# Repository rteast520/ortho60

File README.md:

This is a pcb design and eventual firmware for an ortholinear 60% hall effect keyboard. To my knowledge there currently are no hall effect ortholinear keyboards for purchase so feel free to take this and run with it.

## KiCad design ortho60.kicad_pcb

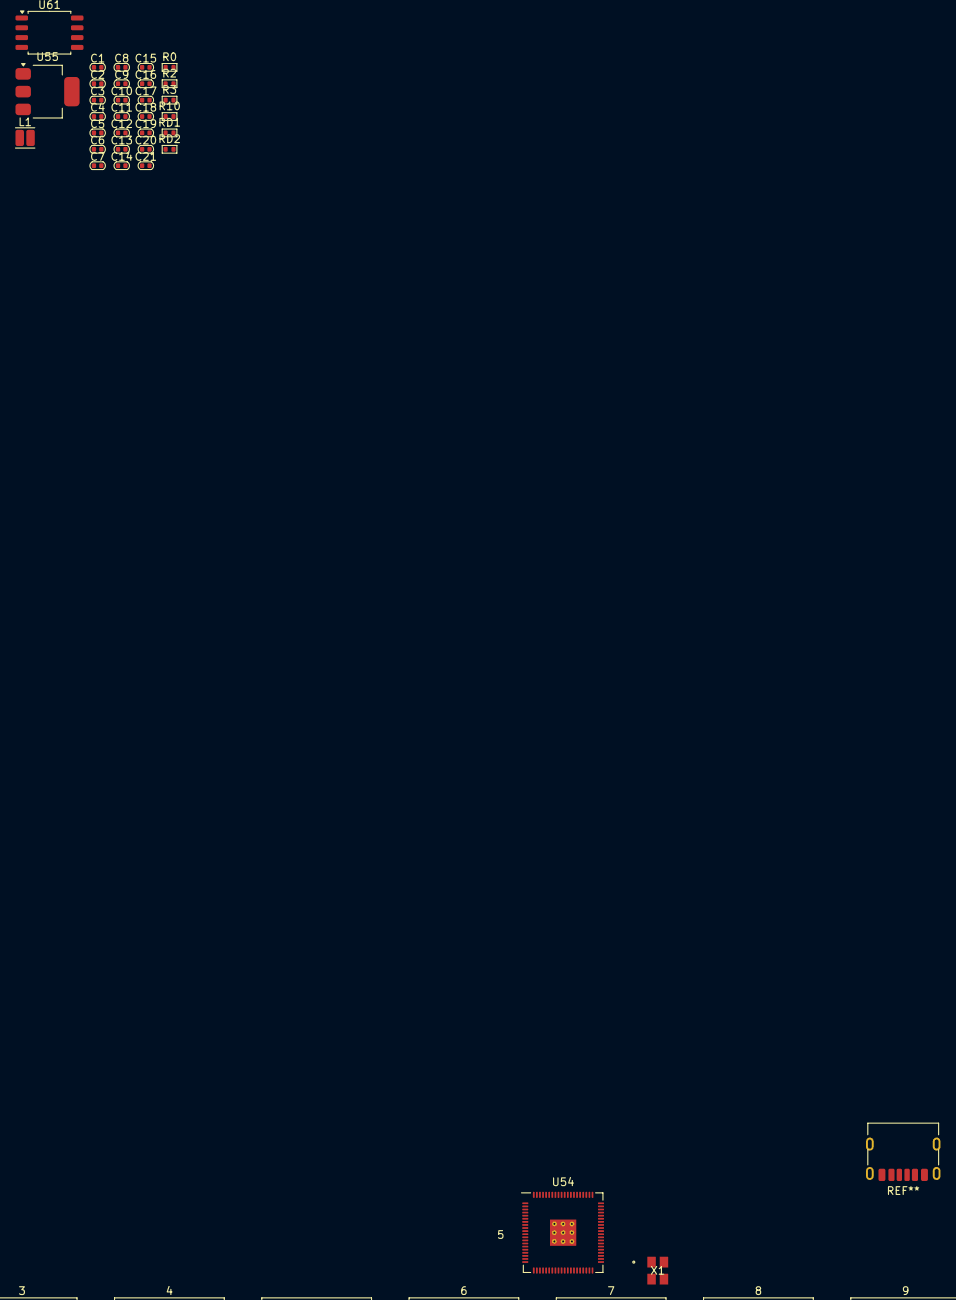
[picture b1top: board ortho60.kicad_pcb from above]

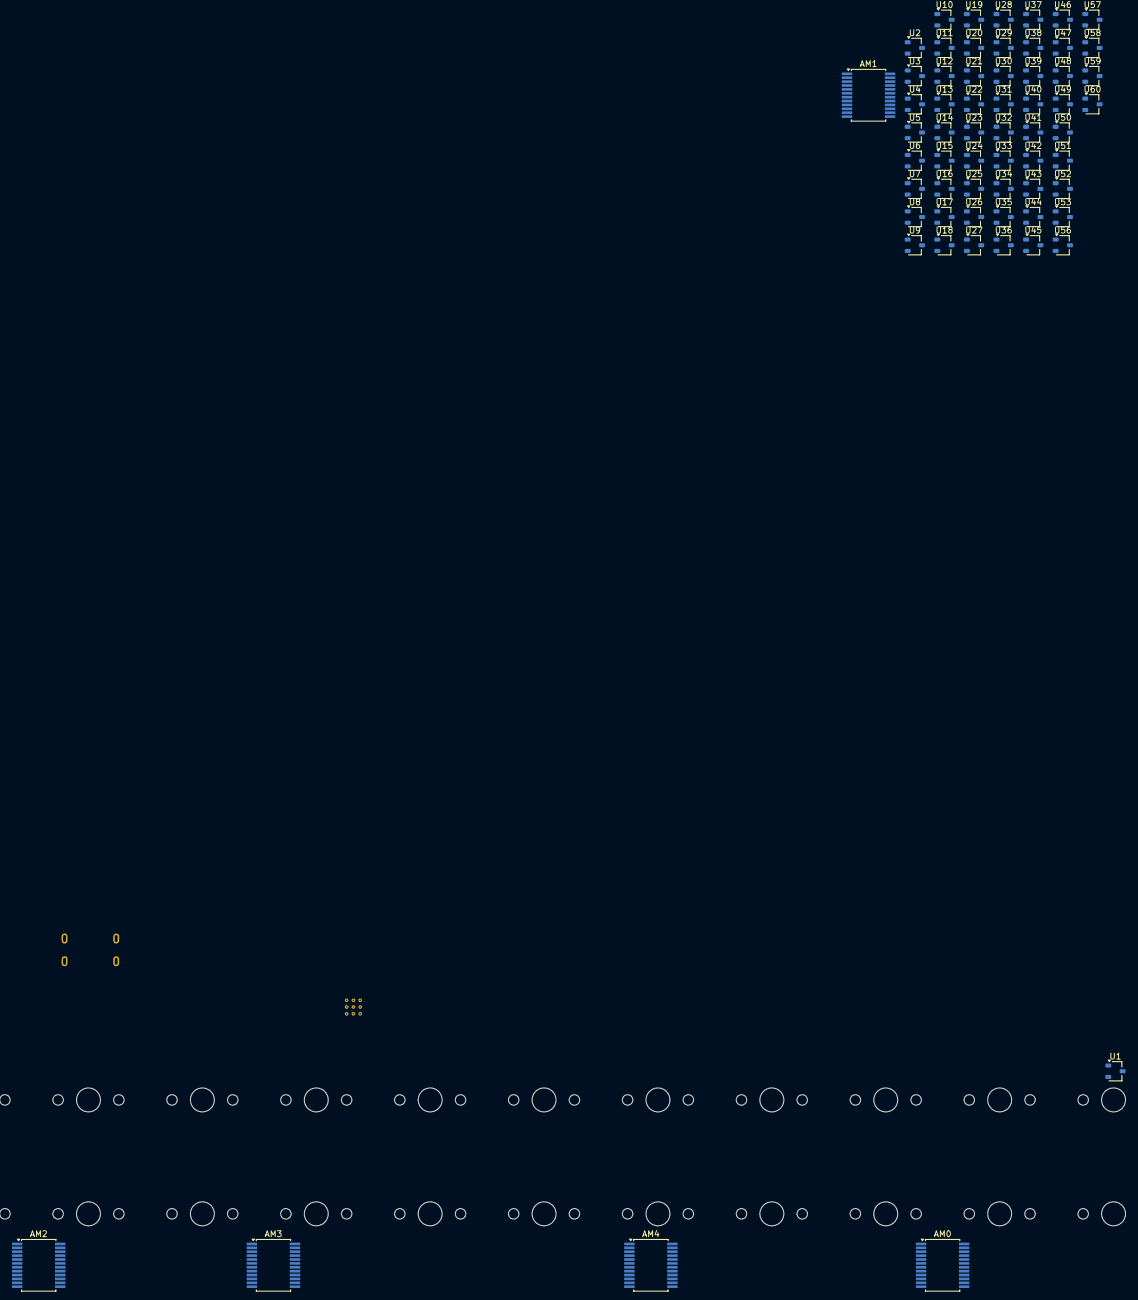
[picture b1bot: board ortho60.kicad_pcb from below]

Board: 2 copper layers, 153 parts (63 on the bottom side), 84 nets, no tracks yet.

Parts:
0, 1, 2, 3, 4, 5, 6, 7, 8, 9, .>: SW_Hal_MX_PCB_1.00u
,<: SW_Hal_MX_PCB_1.00u
->: SW_Hal_MX_PCB_1.00u
-_: SW_Hal_MX_PCB_1.00u
/?: SW_Hal_MX_PCB_1.00u
;:'": SW_Hal_MX_PCB_1.00u
<-: SW_Hal_MX_PCB_1.00u
=+: SW_Hal_MX_PCB_1.00u
A: SW_Hal_MX_PCB_1.00u
ALT: SW_Hal_MX_PCB_1.00u
AM0, AM1, AM2, AM3, AM4: CD74HC4067SM; SSOP-24_5.3x8.2mm_P0.65mm
B: SW_Hal_MX_PCB_1.00u
BACK: SW_Hal_MX_PCB_2.00u
C: SW_Hal_MX_PCB_1.00u
C1, C5: C10u_0402; C_0402_1005Metric
C2, C8, C11, C12, C13, C14, C15, C16, C17, C18, C19, C20, C21: C100n_0402; C_0402_1005Metric
C3: C15P_0402; C_0402_1005Metric
C4: C15p_0402; C_0402_1005Metric
C6: C4.7pf_0402; C_0402_1005Metric
C7, C9: C_0402; C_0402_1005Metric
C10: C4.7u_0402; C_0402_1005Metric
CTRL: SW_Hal_MX_PCB_1.00u
D: SW_Hal_MX_PCB_1.00u
E: SW_Hal_MX_PCB_1.00u
ENTR: SW_Hal_MX_PCB_1.00u
ESC: SW_Hal_MX_PCB_1.00u
F: SW_Hal_MX_PCB_1.00u
FN: SW_Hal_MX_PCB_1.00u
G: SW_Hal_MX_PCB_1.00u
H: SW_Hal_MX_PCB_1.00u
I: SW_Hal_MX_PCB_1.00u
J: SW_Hal_MX_PCB_1.00u
K: SW_Hal_MX_PCB_1.00u
L: SW_Hal_MX_PCB_1.00u
L1: L3.3u; L_Cenker_CKCS201610
M: SW_Hal_MX_PCB_1.00u
N: SW_Hal_MX_PCB_1.00u
O: SW_Hal_MX_PCB_1.00u
P: SW_Hal_MX_PCB_1.00u
Q: SW_Hal_MX_PCB_1.00u
R: SW_Hal_MX_PCB_1.00u
R0, R2, R10: R1K_0402; R_0402_1005Metric
R3: R33_0402; R_0402_1005Metric
RD1, RD2: R27_0402; R_0402_1005Metric
RSHIFT: SW_Hal_MX_PCB_1.00u
S: SW_Hal_MX_PCB_1.00u
SHIFT: SW_Hal_MX_PCB_1.00u
SPACE: SW_Hal_MX_PCB_2.00u
SUPER: SW_Hal_MX_PCB_1.00u
T: SW_Hal_MX_PCB_1.00u
TAB: SW_Hal_MX_PCB_1.00u
U: SW_Hal_MX_PCB_1.00u
U1, U2, U3, U4, U5, U6, U7, U8, U9, U10, U11, U12, U13, U14, U15, U16, U17, U18, U19, U20, U21, U22, U23, U24, U25, U26, U27, U28, U29, U30, U31, U32, U33, U34, U35, U36, U37, U38, U39, U40, U41, U42, U43, U44, U45, U46, U47, U48, U49, U50, U51, U52, U53, U56, U57, U58, U59, U60: A3214xLH; SOT-23W
U54: RP2350_80QFN; RP2350-QFN-80-1EP_10x10_P0.4mm_EP3.4x3.4mm_ThermalVias
U55: NCP1117-3.3_SOT223; SOT-223-3_TabPin2
U61: W25Q128JVS; SOIC-8_5.3x5.3mm_P1.27mm
V: SW_Hal_MX_PCB_1.00u
W: SW_Hal_MX_PCB_1.00u
X: SW_Hal_MX_PCB_1.00u
X1: ABM8-272-T3; ABM8-272-T3_ABR
Y: SW_Hal_MX_PCB_1.00u
Z: SW_Hal_MX_PCB_1.00u
{[}]: SW_Hal_MX_PCB_1.00u
|V: SW_Hal_MX_PCB_1.00u
|^: SW_Hal_MX_PCB_1.00u

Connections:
+1V1: C7.1, C8.1, C10.1, C11.1, L1.1, U54.10 (DVDD), U54.32 (DVDD), U54.51 (DVDD), U54.65 (VREG_FB)
+5V: C1.1, U55.3 (VI)
AM0: AM0.1 (COM), U54.49 (GPIO40_ADC0)
AM0:0: AM0.9 (I0), U1.2 (V_{OUT})
AM0:1: AM0.8 (I1), U2.2 (V_{OUT})
AM0:2: AM0.7 (I2), U3.2 (V_{OUT})
AM0:3: AM0.6 (I3), U13.2 (V_{OUT})
AM0:4: AM0.5 (I4), U14.2 (V_{OUT})
AM0:5: AM0.4 (I5), U15.2 (V_{OUT})
AM0:6: AM0.3 (I6), U25.2 (V_{OUT})
AM0:7: AM0.2 (I7), U26.2 (V_{OUT})
AM0:8: AM0.23 (I8), U27.2 (V_{OUT})
AM0:9: AM0.22 (I9), U37.2 (V_{OUT})
AM0:10: AM0.21 (I10), U38.2 (V_{OUT})
AM0:11: AM0.20 (I11), U39.2 (V_{OUT})
AM0:12: AM0.19 (I12), U49.2 (V_{OUT})
AM0:13: AM0.18 (I13), U50.2 (V_{OUT})
AM0:14: AM0.17 (I14), U51.2 (V_{OUT})
AM0:15: AM0.16 (I15), U52.2 (V_{OUT})
AM1: AM1.1 (COM), U54.52 (GPIO41_ADC1)
AM1:0: AM1.9 (I0), U4.2 (V_{OUT})
AM1:1: AM1.8 (I1), U5.2 (V_{OUT})
AM1:2: AM1.7 (I2), U6.2 (V_{OUT})
AM1:3: AM1.6 (I3), U16.2 (V_{OUT})
AM1:4: AM1.5 (I4), U17.2 (V_{OUT})
AM1:5: AM1.4 (I5), U18.2 (V_{OUT})
AM1:6: AM1.3 (I6), U28.2 (V_{OUT})
AM1:7: AM1.2 (I7), U29.2 (V_{OUT})
AM1:8: AM1.23 (I8), U30.2 (V_{OUT})
AM1:9: AM1.22 (I9), U40.2 (V_{OUT})
AM1:10: AM1.21 (I10), U41.2 (V_{OUT})
AM1:11: AM1.20 (I11), U42.2 (V_{OUT})
AM1:12: AM1.19 (I12), U53.2 (V_{OUT})
AM1:13: AM1.18 (I13), U56.2 (V_{OUT})
AM1:14: AM1.17 (I14), U43.2 (V_{OUT})
AM1:15: AM1.16 (I15), U31.2 (V_{OUT})
AM2: AM2.1 (COM), U54.53 (GPIO42_ADC2)
AM2:0: AM2.9 (I0), U7.2 (V_{OUT})
AM2:1: AM2.8 (I1), U8.2 (V_{OUT})
AM2:2: AM2.7 (I2), U9.2 (V_{OUT})
AM2:3: AM2.6 (I3), U10.2 (V_{OUT})
AM2:4: AM2.5 (I4), U19.2 (V_{OUT})
AM2:5: AM2.4 (I5), U20.2 (V_{OUT})
AM2:6: AM2.3 (I6), U21.2 (V_{OUT})
AM2:7: AM2.2 (I7), U22.2 (V_{OUT})
AM2:8: AM2.23 (I8), U32.2 (V_{OUT})
AM2:9: AM2.22 (I9), U33.2 (V_{OUT})
AM2:10: AM2.21 (I10), U34.2 (V_{OUT})
AM2:11: AM2.20 (I11), U44.2 (V_{OUT})
AM2:12: AM2.19 (I12), U45.2 (V_{OUT})
AM2:13: AM2.18 (I13), U46.2 (V_{OUT})
AM2:14: AM2.17 (I14), U57.2 (V_{OUT})
AM2:15: AM2.16 (I15), U58.2 (V_{OUT})
AM3: AM3.1 (COM), U54.54 (GPIO43_ADC3)
AM3:0: AM3.9 (I0), U11.2 (V_{OUT})
AM3:1: AM3.8 (I1), U12.2 (V_{OUT})
AM3:3: AM3.6 (I3), U23.2 (V_{OUT})
AM3:4: AM3.5 (I4), U24.2 (V_{OUT})
AM3:6: AM3.3 (I6), U35.2 (V_{OUT})
AM3:7: AM3.2 (I7), U36.2 (V_{OUT})
AM3:9: AM3.22 (I9), U47.2 (V_{OUT})
AM3:10: AM3.21 (I10), U48.2 (V_{OUT})
AM3:12: AM3.19 (I12), U59.2 (V_{OUT})
AM3:13: AM3.18 (I13), U60.2 (V_{OUT})
GND: AM0.12 (GND), AM0.15 (~E), AM1.12 (GND), AM1.15 (~E), AM2.12 (GND), AM2.15 (~E), AM3.4 (I5), AM3.7 (I2), AM3.12 (GND), AM3.15 (~E), AM3.16 (I15), AM3.17 (I14), AM3.20 (I11), AM3.23 (I8), AM4.12 (GND), AM4.15 (~E), C1.2, C2.1, C3.2, C4.1, C5.2, C6.2, C7.2, C8.2, C9.2, C10.2, C11.2, C12.2, C13.2, C14.2, C15.2, C16.2, C17.2, C18.2, C19.2, C20.2, C21.2, U1.3 (GND), U2.3 (GND), U3.3 (GND), U4.3 (GND), U5.3 (GND), U6.3 (GND), U7.3 (GND), U8.3 (GND), U9.3 (GND), U10.3 (GND), U11.3 (GND), U12.3 (GND), U13.3 (GND), U14.3 (GND), U15.3 (GND), U16.3 (GND), U17.3 (GND), U18.3 (GND), U19.3 (GND), U20.3 (GND), U21.3 (GND), U22.3 (GND), U23.3 (GND), U24.3 (GND), U25.3 (GND), U26.3 (GND), U27.3 (GND), U28.3 (GND), U29.3 (GND), U30.3 (GND), U31.3 (GND), U32.3 (GND), U33.3 (GND), U34.3 (GND), U35.3 (GND), U36.3 (GND), U37.3 (GND), U38.3 (GND), U39.3 (GND), U40.3 (GND), U41.3 (GND), U42.3 (GND), U43.3 (GND), U44.3 (GND), U45.3 (GND), U46.3 (GND), U47.3 (GND), U48.3 (GND), U49.3 (GND), U50.3 (GND), U51.3 (GND), U52.3 (GND), U53.3 (GND), U54.62 (VREG_PGND), U55.1 (GND), U56.3 (GND), U57.3 (GND), U58.3 (GND), U59.3 (GND), U60.3 (GND), U61.4 (GND), X1.2, X1.4
GPIO1: AM0.24 (VCC), AM1.24 (VCC), AM2.24 (VCC), AM3.24 (VCC), AM4.24 (VCC), C2.2, C6.1, C12.1, C13.1, C14.1, C15.1, C16.1, C17.1, C18.1, C19.1, C20.1, C21.1, R3.2, R10.1, U1.1 (V_{CC}), U2.1 (V_{CC}), U3.1 (V_{CC}), U4.1 (V_{CC}), U5.1 (V_{CC}), U6.1 (V_{CC}), U7.1 (V_{CC}), U8.1 (V_{CC}), U9.1 (V_{CC}), U10.1 (V_{CC}), U11.1 (V_{CC}), U12.1 (V_{CC}), U13.1 (V_{CC}), U14.1 (V_{CC}), U15.1 (V_{CC}), U16.1 (V_{CC}), U17.1 (V_{CC}), U18.1 (V_{CC}), U19.1 (V_{CC}), U20.1 (V_{CC}), U21.1 (V_{CC}), U22.1 (V_{CC}), U23.1 (V_{CC}), U24.1 (V_{CC}), U25.1 (V_{CC}), U26.1 (V_{CC}), U27.1 (V_{CC}), U28.1 (V_{CC}), U29.1 (V_{CC}), U30.1 (V_{CC}), U31.1 (V_{CC}), U32.1 (V_{CC}), U33.1 (V_{CC}), U34.1 (V_{CC}), U35.1 (V_{CC}), U36.1 (V_{CC}), U37.1 (V_{CC}), U38.1 (V_{CC}), U39.1 (V_{CC}), U40.1 (V_{CC}), U41.1 (V_{CC}), U42.1 (V_{CC}), U43.1 (V_{CC}), U44.1 (V_{CC}), U45.1 (V_{CC}), U46.1 (V_{CC}), U47.1 (V_{CC}), U48.1 (V_{CC}), U49.1 (V_{CC}), U50.1 (V_{CC}), U51.1 (V_{CC}), U52.1 (V_{CC}), U53.1 (V_{CC}), U54.5 (IOVDD), U54.15 (IOVDD), U54.24 (IOVDD), U54.29 (IOVDD), U54.41 (IOVDD), U54.50 (IOVDD), U54.59 (ADC_AVDD), U54.60 (IOVDD), U54.64 (VREG_VIN), U54.68 (USB_OTP_VDD), U54.69 (QSPI_IOVDD), U54.76 (IOVDD), U54.78 (GPIO1), U56.1 (V_{CC}), U57.1 (V_{CC}), U58.1 (V_{CC}), U59.1 (V_{CC}), U60.1 (V_{CC}), U61.1 (~CS), U61.8 (VCC)
unnamed: C3.1, R2.2, X1.3
unnamed: RD2.2, U54.66 (USB_DM)
unnamed: RD1.2, U54.67 (USB_DP)
unnamed: C9.1, R3.1, U54.61 (VREG_AVDD)
unnamed: L1.2, U54.63 (VREG_LX)
unnamed: C5.1, U55.2 (VO)
QSPI_SCLK: U54.71 (QSPI_SCLK), U61.6 (CLK)
QSPI_SD0: U54.72 (QSPI_SD0), U61.5 (DI/IO_{0})
QSPI_SD1: U54.74 (QSPI_SD1), U61.2 (DO/IO_{1})
QSPI_SD2: U54.73 (QSPI_SD2), U61.3 (~WP/IO_{2})
QSPI_SD3: U54.70 (QSPI_SD3), U61.7 (~HOLD/~RESET/IO_{3})
QSPI_SS: R0.2, R10.2, U54.75 (QSPI_SS)
SELECT0: AM0.10 (S0), AM1.10 (S0), AM2.10 (S0), AM3.10 (S0), AM4.10 (S0)
SELECT1: AM0.11 (S1), AM1.11 (S1), AM2.11 (S1), AM3.11 (S1), AM4.11 (S1)
SELECT2: AM0.14 (S2), AM1.14 (S2), AM2.14 (S2), AM3.14 (S2), AM4.14 (S2)
SELECT3: AM0.13 (S3), AM1.13 (S3), AM2.13 (S3), AM3.13 (S3), AM4.13 (S3)
XIN: C4.2, U54.30 (XIN), X1.1
XOUT: R2.1, U54.31 (XOUT)

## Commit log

2025-07-20 Initial commit for project includes all pcb design before traces have been done. Firmware start to follow
2025-07-20 Create README.md
    added a readme
2025-07-20 Added generic main.c for firmware
2025-07-23 First ideas for reading from adc's for pico
2025-07-23 Added last reading tracker to key presses
